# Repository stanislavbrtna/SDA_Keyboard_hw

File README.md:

# SDA Keyboard HW
This repo contains hardware part of the SDA Keyboard addon.

## Useful links 
[SDA Keyboard SW](https://github.com/stanislavbrtna/SDA_Keyboard_sw)

[SDA Project page on hackaday.io](https://hackaday.io/project/35165-sda-the-best-new-pda)

[SDA_OS Repository](https://github.com/stanislavbrtna/SDA_OS)

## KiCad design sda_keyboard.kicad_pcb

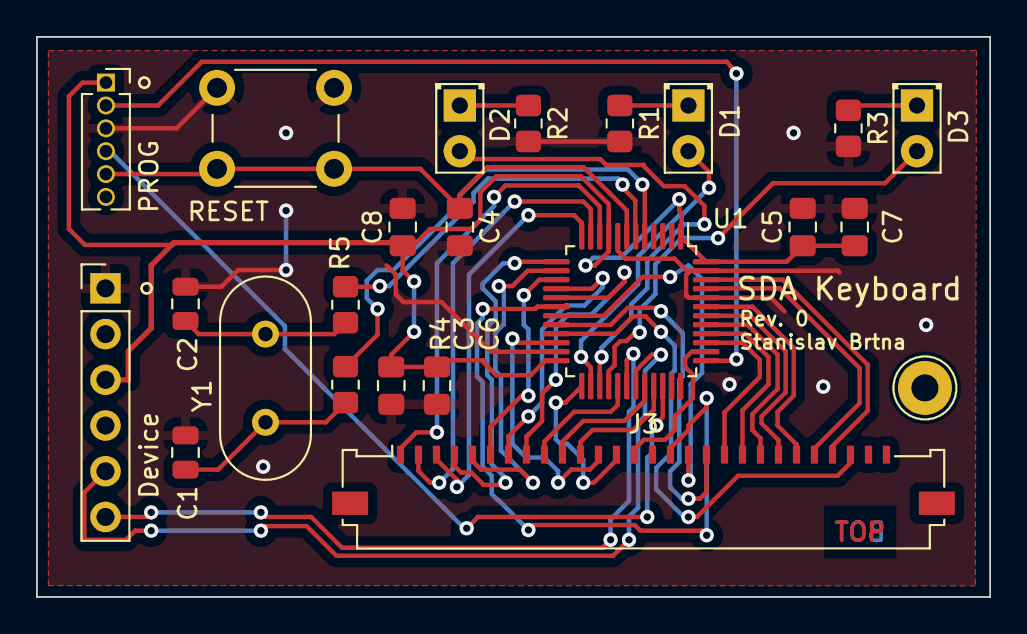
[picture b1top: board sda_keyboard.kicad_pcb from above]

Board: 2 copper layers, 53.0 x 31.1 mm, 22 parts (0 on the bottom side), 42 nets.

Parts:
C1, C2: C; C_0805_2012Metric
C3, C4, C5: 100n; C_0805_2012Metric_Pad1.18x1.45mm_HandSolder
C6: 10n; C_0805_2012Metric_Pad1.18x1.45mm_HandSolder
C7: 4.7u; C_0805_2012Metric_Pad1.18x1.45mm_HandSolder
C8: 1u; C_0805_2012Metric_Pad1.18x1.45mm_HandSolder
D1, D2, D3: LED; LED_D2.0mm_W4.8mm_H2.5mm_FlatTop
Device: Device_conn; PinHeader_1x06_P2.54mm_Vertical
J3: Conn_01x28; Molex_200528-0280_1x28-1MP_P1.00mm_Horizontal
PROG: Prog; PinSocket_1x06_P1.27mm_Vertical
R1, R2, R3, R4, R5: R; R_0805_2012Metric_Pad1.20x1.40mm_HandSolder
RESET: RESET; SW_PUSH_6mm_H9.5mm
U1: STM32F051C8Tx; LQFP-48_7x7mm_P0.5mm
Y1: Crystal; Crystal_HC18-U_Vertical

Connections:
+3.3V: C3.1, C5.1, C6.1, C7.1, C8.1, Device.3, PROG.1, U1.1 (VBAT), U1.9 (VDDA), U1.24 (VDD), U1.48 (VDD)
Conn_RX: Device.6, U1.30 (PA9)
Conn_Tx: Device.5, U1.31 (PA10)
GND: C1.2, C2.2, C3.2, C4.2, C5.2, C6.2, C7.2, C8.2, Device.1, PROG.3, R1.2, R2.2, R3.2, RESET.1, U1.8 (VSSA), U1.23 (VSS), U1.44 (BOOT0), U1.47 (VSS)
Kbd_01: J3.1, U1.10 (PA0)
Kbd_02: J3.2, U1.11 (PA1)
Kbd_03: J3.3, U1.12 (PA2)
Kbd_04: J3.4, U1.13 (PA3)
Kbd_05: J3.5, U1.14 (PA4)
Kbd_06: J3.6, U1.15 (PA5)
Kbd_07: J3.7, U1.16 (PA6)
Kbd_08: J3.8, U1.17 (PA7)
Kbd_09: J3.9, U1.29 (PA8)
Kbd_10: J3.10, U1.32 (PA11)
Kbd_11: J3.11, U1.33 (PA12)
Kbd_12: J3.12, U1.22 (PB11)
Kbd_13: J3.13, U1.25 (PB12)
Kbd_14: J3.14, U1.38 (PA15)
Kbd_15: J3.16, U1.18 (PB0)
Kbd_16: J3.17, U1.19 (PB1)
Kbd_17: J3.18, U1.20 (PB2)
Kbd_18: J3.19, U1.39 (PB3)
Kbd_19: J3.20, U1.40 (PB4)
Kbd_20: J3.21, U1.41 (PB5)
Kbd_21: J3.22, U1.42 (PB6)
Kbd_22: J3.23, U1.43 (PB7)
Kbd_23: J3.24, U1.45 (PB8)
Kbd_24: J3.25, U1.46 (PB9)
Kbd_25: J3.26, U1.21 (PB10)
Led_01: D1.2 (A), U1.26 (PB13)
Led_02: D2.2 (A), U1.27 (PB14)
Led_03: D3.2 (A), U1.28 (PB15)
unnamed: C1.1, R4.2, Y1.1
unnamed: C2.1, R5.2, Y1.2
unnamed: D1.1 (K), R1.1
unnamed: D2.1 (K), R2.1
unnamed: D3.1 (K), R3.1
unnamed: R4.1, U1.5 (PF0)
unnamed: R5.1, U1.6 (PF1)
RESET: C4.1, PROG.5, RESET.2, U1.7 (NRST)
SWD_TCK: PROG.2, U1.37 (PA14)
SWD_TMS: PROG.4, U1.34 (PA13)

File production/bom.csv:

Designator,Footprint,Quantity,Value,LCSC Part #
C1,0805,1,C,
C2,0805,1,C,
C3,0805,1,100n,
C4,0805,1,100n,
C5,0805,1,100n,
C6,0805,1,10n,
C7,0805,1,4.7u,
C8,0805,1,1u,
"D1, D2, D3",LED_D2.0mm_W4.8mm_H2.5mm_FlatTop,3,LED,
Device,PinHeader_1x06_P2.54mm_Vertical,1,Device_conn,
J3,Molex_200528-0280_1x28-1MP_P1.00mm_Horizontal,1,Conn_01x28,
PROG,PinSocket_1x06_P1.27mm_Vertical,1,Prog,
R1,0805,1,R,
R2,0805,1,R,
R3,0805,1,R,
R4,0805,1,R,
R5,0805,1,R,
RESET,SW_PUSH_6mm_H9.5mm,1,RESET,
U1,LQFP-48_7x7mm_P0.5mm,1,STM32F051C8Tx,
Y1,Crystal_HC18-U_Vertical,1,Crystal,

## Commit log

2023-06-25 readme added
